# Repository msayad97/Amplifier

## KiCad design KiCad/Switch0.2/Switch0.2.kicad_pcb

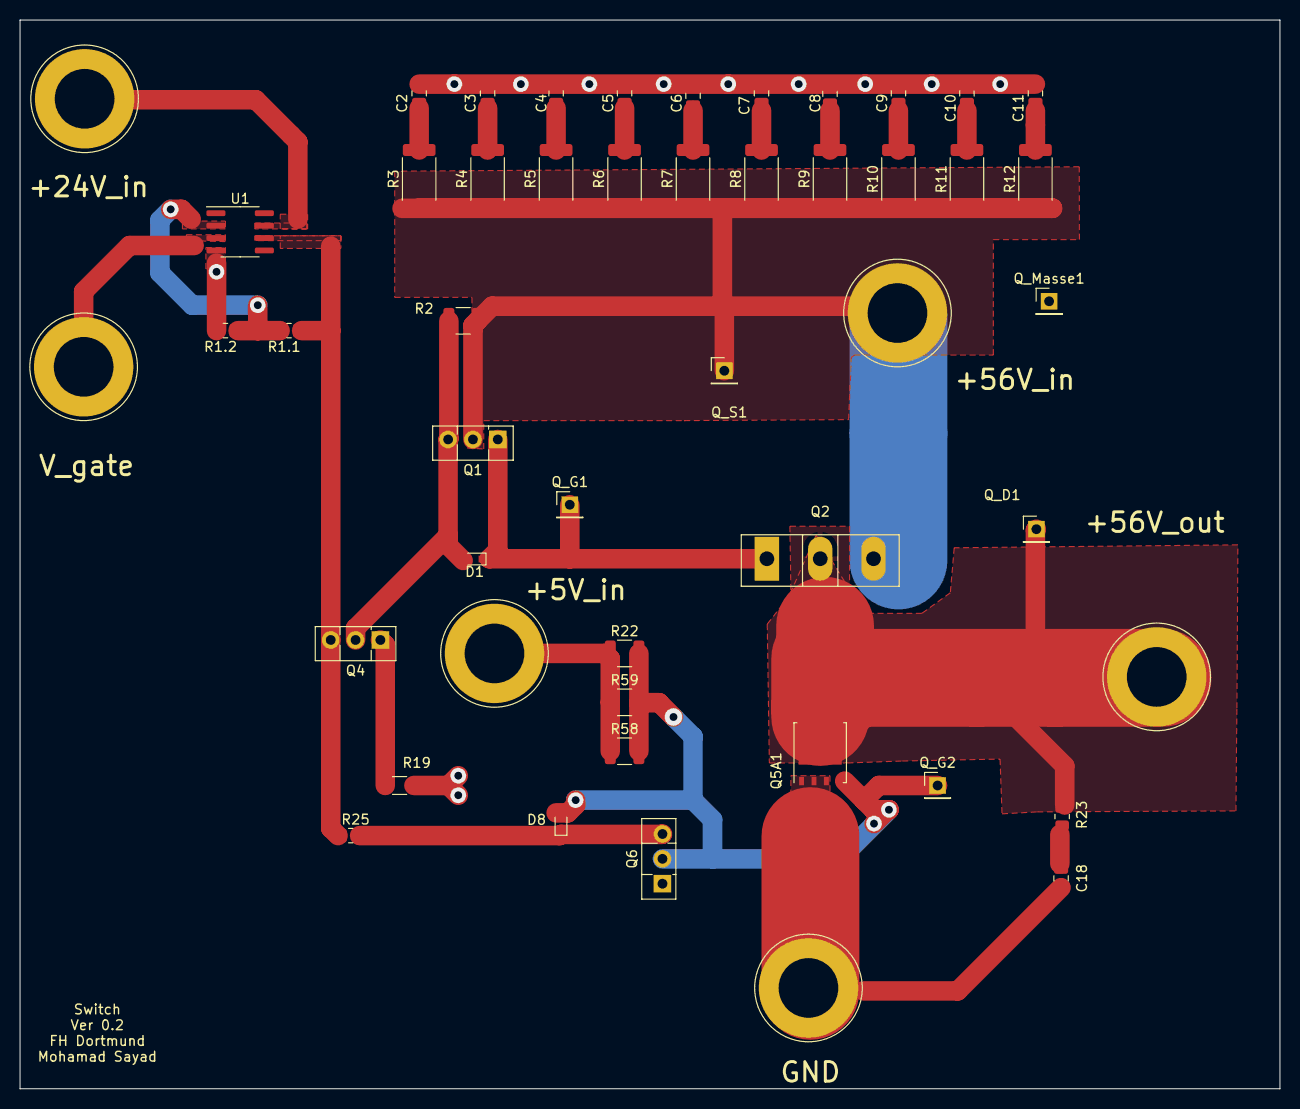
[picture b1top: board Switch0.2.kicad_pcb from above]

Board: 2 copper layers, 128.8 x 109.2 mm, 49 parts (0 on the bottom side), 24 nets.

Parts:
+5V_in, +24V_in, +56V_in, +56V_out: Conn_01x01; Banana_Jack_1Pin
C2, C3, C4, C5, C6, C7, C8, C9, C10, C11: 0.1uF; C_0805_2012Metric
C18: 1nF; C_0805_2012Metric
D1, D8: type="D" model="BAT54XV2T5G" lib=""; D_SOD-523_new
GND: Conn_01x01; Banana_Jack_1Pin
Q1, Q4, Q6: BD139; TO-126-3_Vertical
Q2: IXTH90P10P; TO-247-3_MOSFET
Q5A1: BSC340N08NS3G; TDSON-8-1
Q_D1: Conn_01x01; PinHeader_1x01_P2.54mm_Vertical
Q_G1, Q_G2: Conn_01x01; PinHeader_1x01_P2.54mm_Vertical
Q_Masse1: Conn_01x01; PinHeader_1x01_P2.54mm_Vertical
Q_S1: Conn_01x01; PinHeader_1x01_P2.54mm_Vertical
R1.1: 10k; R_0805_2012Metric
R1.2: 2k; R_0805_2012Metric
R2: 330R; R_1210_3225Metric
R3, R4, R5, R6, R7, R8, R9, R10, R11, R12: 2R2; R_2512_6332Metric
R19: 120R; R_1206_3216Metric
R22, R58, R59: 220R; R_1210_3225Metric
R23: 2R2; R_0805_2012Metric
R25: 4k7; R_0805_2012Metric
U1: AD8033; SOIC-8_3.9x4.9mm_P1.27mm
V_gate: Conn_01x01; Banana_Jack_1Pin

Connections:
56V: +56V_in.1, Q1.2 (C), Q2.3 (D), Q_S1.1, R2.1, R3.1, R4.1, R5.1, R6.1, R7.1, R8.1, R9.1, R10.1, R11.1, R12.1
D: +56V_out.1, Q2.1 (S), Q5A1.5 (D), Q_D1.1, R23.1
G1: D1.1 (A), Q1.1 (E), Q2.2 (G), Q_G1.1
G2: D8.2 (K), Q5A1.4 (G), Q6.2 (C), Q_G2.1, R22.2, R58.2, R59.2
GND: C2.2, C3.2, C4.2, C5.2, C6.2, C7.2, C8.2, C9.2, C10.2, C11.2, C18.2, GND.1, Q5A1.1 (S), Q5A1.2 (S), Q5A1.3 (S), Q6.1 (E), Q_Masse1.1, R1.2.2, R19.2, U1.4 (V-)
unnamed: C2.1, R3.2
unnamed: C3.1, R4.2
unnamed: C4.1, R5.2
unnamed: C5.1, R6.2
unnamed: C6.1, R7.2
unnamed: C7.1, R8.2
unnamed: C8.1, R9.2
unnamed: C9.1, R10.2
unnamed: C10.1, R11.2
unnamed: C11.1, R12.2
unnamed: C18.1, R23.2
unnamed: D1.2 (K), Q1.3 (B), Q4.2 (C), R2.2
unnamed: D8.1 (A), Q6.3 (B), R25.2
unnamed: Q4.3 (B), R1.1.1, R25.1, U1.6
unnamed: Q4.1 (E), R19.1
unnamed: R1.1.2, R1.2.1, U1.2 (-)
unnamed: +24V_in.1, U1.7 (V+)
Tackt: U1.3 (+), V_gate.1
Vp: +5V_in.1, R22.1, R58.1, R59.1
